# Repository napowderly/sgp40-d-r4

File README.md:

# sgp40-d-r4

Wooohooo a new package!

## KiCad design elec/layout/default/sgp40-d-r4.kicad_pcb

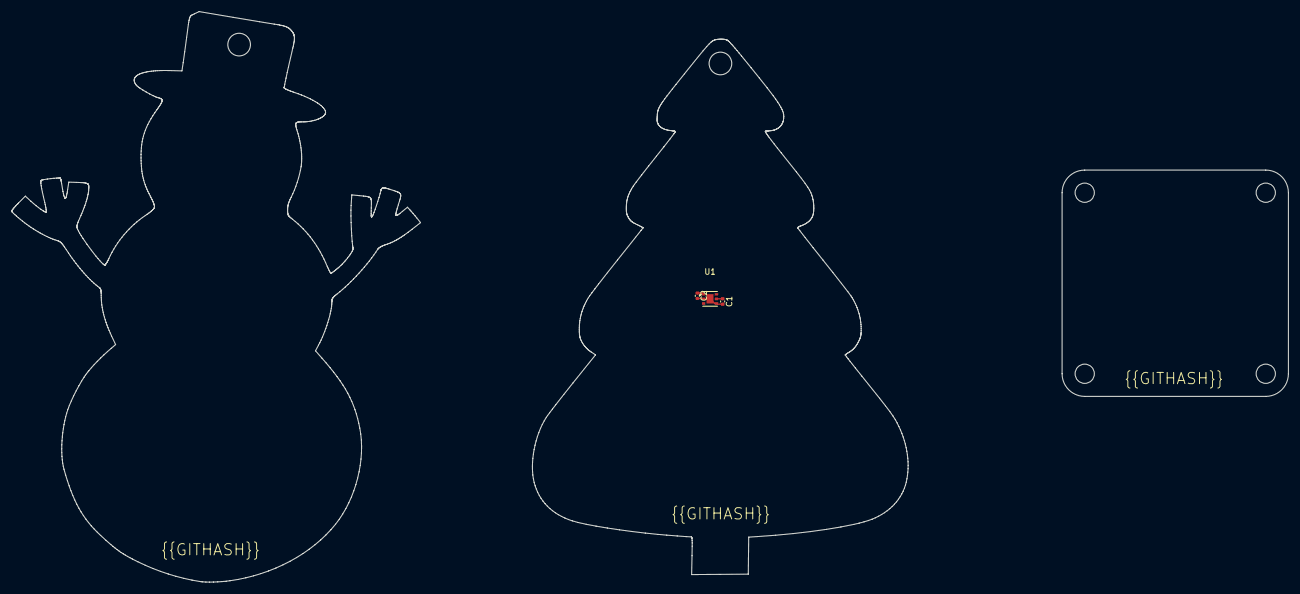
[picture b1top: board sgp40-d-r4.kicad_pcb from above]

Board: 2 copper layers, 66.4 x 94.6 mm, 3 parts (0 on the bottom side), 2 nets.

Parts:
C1, C2: Multilayer Ceramic Capacitors MLCC - SMD/SMT 1uF 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; C0402
U1: DFN-6_L2.4-W2.4-P0.80-TL-EP

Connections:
gnd: C1.2, C2.2, U1.2, U1.4, U1.7
vcc: C1.1, C2.1, U1.1, U1.5

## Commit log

2024-02-13 Configure project
2024-02-15 layout
